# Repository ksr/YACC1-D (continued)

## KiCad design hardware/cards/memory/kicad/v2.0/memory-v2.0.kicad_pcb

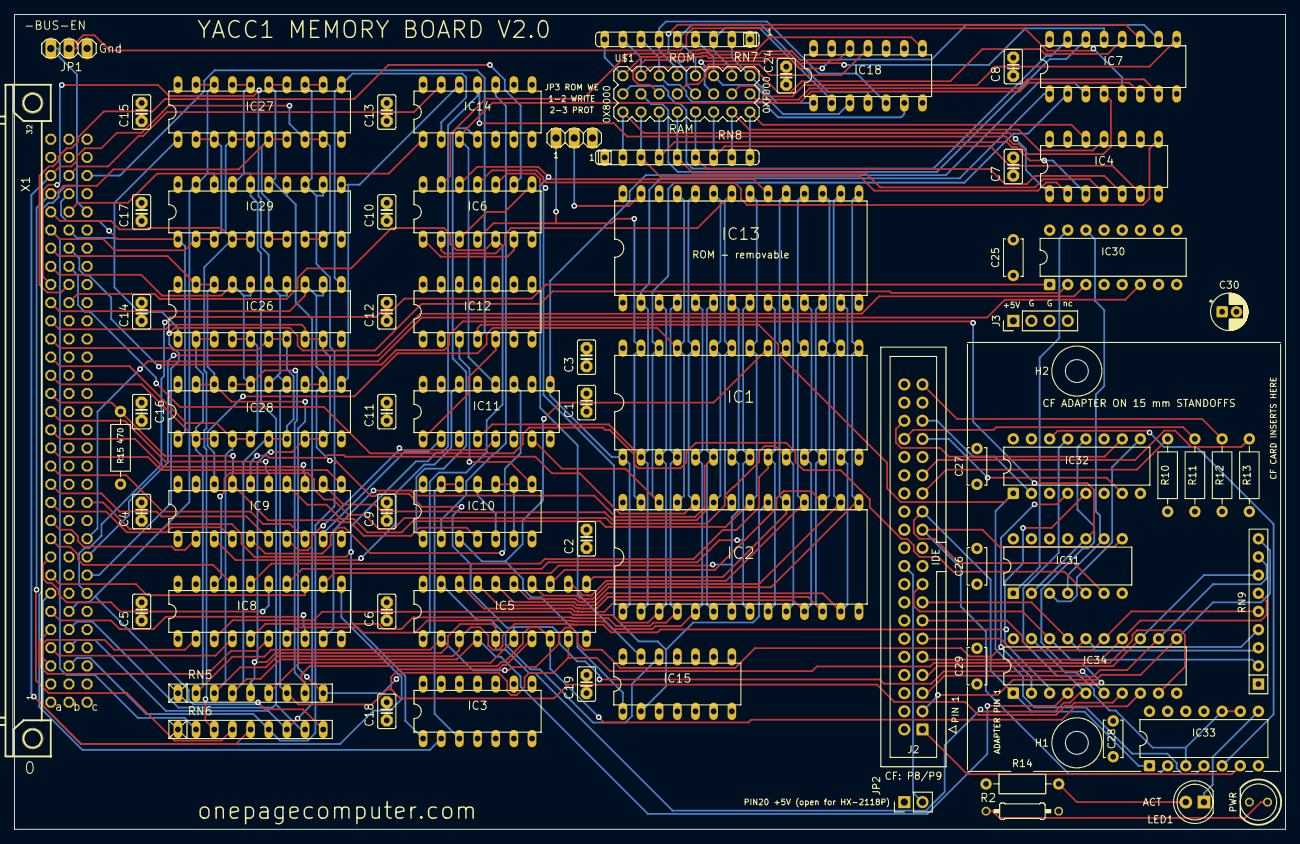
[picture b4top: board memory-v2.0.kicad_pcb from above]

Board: 4 copper layers, 177.8 x 114.0 mm, 74 parts (0 on the bottom side), 149 nets.

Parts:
C1, C2, C3, C4, C5, C6, C7, C8, C9, C10, C11, C12, C13, C14, C15, C16, C17, C18, C19, C24: C025-025X050
C25, C26, C27, C28, C29: 100n; C_Disc_D5.0mm_W2.5mm_P5.00mm
C30: 10u; CP_Radial_D5.0mm_P2.00mm
H1, H2: M3 standoff 15 mm (CF adapter); MountingHole_3.2mm_M3
IC1, IC2, IC13: DIL28-6
IC3: 74LS32N; DIL14
IC4, IC18: 74ALS30N; DIL14
IC5: 74LS245N; DIL20
IC6, IC14: 74LS04N; DIL14
IC7: 74LS138N; DIL16
IC8, IC9: 74LS244N; DIL20
IC10: 74ALS00N; DIL14
IC11: 74LS157N; DIL16
IC12: 74LS74N; DIL14
IC15: 74ALS11N; DIL14
IC26, IC27, IC28, IC29: 74LS374N; DIL20
IC30: 74LS138; DIP-16_W7.62mm
IC31: 74LS32; DIP-14_W7.62mm
IC32: 74LS175; DIP-16_W7.62mm
IC33: 74LS08; DIP-14_W7.62mm
IC34: 74LS245; DIP-20_W7.62mm
J2: IDE 40; IDC-Header_2x20_P2.54mm_Vertical
J3: POWER; PinHeader_1x04_P2.54mm_Vertical
JP1: 1X03
JP2: PIN20 5V; PinHeader_1x02_P2.54mm_Vertical
JP3: PINHD-1X3; 1X03
LED1: ACT yellow; LED_D5.0mm
PWR0: LED5MM
R2: 330; 0207_10
R10, R11, R12, R13: 10k; R_Axial_DIN0207_L6.3mm_D2.5mm_P10.16mm_Horizontal
R14: 1k; R_Axial_DIN0207_L6.3mm_D2.5mm_P10.16mm_Horizontal
R15: 470; R_Axial_DIN0207_L6.3mm_D2.5mm_P10.16mm_Horizontal
RN5, RN6: RN-9
RN7, RN8: SIL9
RN9: 10k x8; R_Array_SIP9
U$1: PIN_3X8
X1: FABC96R

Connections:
-BUS-EN: IC3.2, JP1.1, X1.C28
-HI-RAM: IC2.20, IC6.10, IC15.2
-IO-RD: IC31.5, X1.B25
-IO-WR: IC31.2, IC31.10, X1.B26
-LO-RAM: IC1.20, IC10.3, IC15.1
-MEM-RD: IC5.1, IC6.5, X1.B23
-MEM-WR: IC6.9, X1.B24
-RESET: IC12.4, IC32.1, IC33.4, X1.C30
-ROM-CS: IC6.12, IC13.20, IC15.13
-TMP-REG-LD0: IC14.1, X1.B28
-TMP-REG-LD1: IC14.13, X1.B30
-TMP-REG-RD0: IC26.1, IC27.1, X1.B27
-TMP-REG-RD1: IC28.1, IC29.1, X1.B29
-VMA: IC3.1, IC7.4, IC14.11, X1.C12
/Sheet 2/RAM0: IC4.1, RN8.2, U$1.17
/Sheet 2/RAM1: IC4.2, RN8.3, U$1.18
/Sheet 2/RAM2: IC4.3, RN8.4, U$1.19
/Sheet 2/RAM3: IC4.4, RN8.5, U$1.20
/Sheet 2/RAM4: IC4.5, RN8.6, U$1.21
/Sheet 2/RAM5: IC4.6, RN8.7, U$1.22
/Sheet 2/RAM6: IC4.11, RN8.8, U$1.23
/Sheet 2/RAM7: IC4.12, RN8.9, U$1.24
/Sheet 2/ROM0: IC18.12, RN7.9, U$1.1
/Sheet 2/ROM1: IC18.11, RN7.8, U$1.2
/Sheet 2/ROM2: IC18.6, RN7.7, U$1.3
/Sheet 2/ROM3: IC18.5, RN7.6, U$1.4
/Sheet 2/ROM4: IC18.4, RN7.5, U$1.5
/Sheet 2/ROM5: IC18.3, RN7.4, U$1.6
/Sheet 2/ROM6: IC18.2, RN7.3, U$1.7
/Sheet 2/ROM7: IC18.1, RN7.2, U$1.8
/Sheet 2/SEL0: IC7.15, U$1.9
/Sheet 2/SEL1: IC7.14, U$1.10
/Sheet 2/SEL2: IC7.13, U$1.11
/Sheet 2/SEL3: IC7.12, U$1.12
/Sheet 2/SEL4: IC7.11, U$1.13
/Sheet 2/SEL5: IC7.10, U$1.14
/Sheet 2/SEL6: IC7.9, U$1.15
/Sheet 2/SEL7: IC7.7, U$1.16
/Sheet 3/ROM-WE: IC13.27, JP3.2
/Sheet 7/-CFOE: IC33.3, IC33.9, IC33.10, IC34.19
/Sheet 7/-CFRESET: IC33.6, J2.1
/Sheet 7/-DASP: J2.39, R12.2
/Sheet 7/-DMACK: J2.29, R13.2
/Sheet 7/-IOR: IC31.6, IC33.1, IC34.1, J2.25
/Sheet 7/-IOW: IC31.8, IC33.2, J2.23
/Sheet 7/-P8SEL: IC30.15, IC31.1
/Sheet 7/-P9SEL: IC30.14, IC31.4, IC31.9
/Sheet 7/-PDIAG: J2.34, R11.2
/Sheet 7/-SRST: IC32.14, IC33.5
/Sheet 7/ACTK: IC33.8, LED1.1
/Sheet 7/CFD0: IC34.18, J2.17, RN9.2
/Sheet 7/CFD1: IC34.17, J2.15, RN9.3
/Sheet 7/CFD2: IC34.16, J2.13, RN9.4
/Sheet 7/CFD3: IC34.15, J2.11, RN9.5
/Sheet 7/CFD4: IC34.14, J2.9, RN9.6
/Sheet 7/CFD5: IC34.13, J2.7, RN9.7
/Sheet 7/CFD6: IC34.12, J2.5, RN9.8
/Sheet 7/CFD7: IC34.11, J2.3, RN9.9
/Sheet 7/DA0: IC32.2, J2.35
/Sheet 7/DA1: IC32.7, J2.33
/Sheet 7/DA2: IC32.10, J2.36
/Sheet 7/IORDY: J2.27, R10.2
/Sheet 7/LATCHCLK: IC31.3, IC32.9
/Sheet 7/LEDA2: LED1.2, R14.2
/Sheet 7/PIN20: J2.20, JP2.2
ADDR0: IC8.2, X1.A3
ADDR1: IC8.4, X1.A4
ADDR2: IC8.6, X1.A5
ADDR3: IC8.8, X1.A6
ADDR4: IC8.11, X1.A7
ADDR5: IC8.13, X1.A8
ADDR6: IC8.15, X1.A9
ADDR7: IC8.17, X1.A10
ADDR8: IC9.2, X1.A11
ADDR9: IC9.4, X1.A12
ADDR10: IC9.6, X1.A13
ADDR11: IC9.8, X1.A14
ADDR12: IC9.11, X1.A15
ADDR13: IC9.13, X1.A16
ADDR14: IC9.15, X1.A17
ADDR15: IC9.17, IC10.4, R15.1, X1.A18
BADDR0: IC1.10, IC2.10, IC8.18, IC13.10
BADDR1: IC1.9, IC2.9, IC8.16, IC13.9
BADDR2: IC1.8, IC2.8, IC8.14, IC13.8
BADDR3: IC1.7, IC2.7, IC8.12, IC13.7
BADDR4: IC1.6, IC2.6, IC8.9, IC13.6
BADDR5: IC1.5, IC2.5, IC8.7, IC13.5
BADDR6: IC1.4, IC2.4, IC8.5, IC13.4
BADDR7: IC1.3, IC2.3, IC8.3, IC13.3
BADDR8: IC1.25, IC2.25, IC9.18, IC13.25
BADDR9: IC1.24, IC2.24, IC9.16, IC13.24
BADDR10: IC1.21, IC2.21, IC9.14, IC13.21
BADDR11: IC1.23, IC2.23, IC9.12, IC13.23
BADDR12: IC1.2, IC2.2, IC7.1, IC11.4, IC13.2
BADDR13: IC1.26, IC2.26, IC7.2, IC11.7
BADDR14: IC1.1, IC2.1, IC7.3, IC11.9
BADDR15: IC7.6, IC11.12, IC14.3
BDATA0: IC1.11, IC2.11, IC5.18, IC13.11
BDATA1: IC1.12, IC2.12, IC5.17, IC13.12
BDATA2: IC1.13, IC2.13, IC5.16, IC13.13
BDATA3: IC1.15, IC2.15, IC5.15, IC13.15
BDATA4: IC1.16, IC2.16, IC5.14, IC13.16
BDATA5: IC1.17, IC2.17, IC5.13, IC13.17
BDATA6: IC1.18, IC2.18, IC5.12, IC13.18
BDATA7: IC1.19, IC2.19, IC5.11, IC13.19
DATA0: IC5.2, IC26.2, IC26.3, IC28.2, IC28.3, IC32.4, IC34.2, RN5.2, X1.A19
DATA1: IC5.3, IC26.4, IC26.5, IC28.4, IC28.5, IC32.5, IC34.3, RN5.3, X1.A20
DATA2: IC5.4, IC26.6, IC26.7, IC28.6, IC28.7, IC32.12, IC34.4, RN5.4, X1.A21
DATA3: IC5.5, IC26.8, IC26.9, IC28.8, IC28.9, IC32.13, IC34.5, RN5.5, X1.A22
DATA4: IC5.6, IC26.12, IC26.13, IC28.12, IC28.13, IC34.6, RN5.6, X1.A23
DATA5: IC5.7, IC26.14, IC26.15, IC28.14, IC28.15, IC34.7, RN5.7, X1.A24
DATA6: IC5.8, IC26.16, IC26.17, IC28.16, IC28.17, IC34.8, RN5.8, X1.A25
DATA7: IC5.9, IC26.18, IC26.19, IC28.18, IC28.19, IC34.9, RN5.9, X1.A26
DATA8: IC27.2, IC27.3, IC29.2, IC29.3, RN6.2, X1.A27
DATA9: IC27.4, IC27.5, IC29.4, IC29.5, RN6.3, X1.A28
DATA10: IC27.6, IC27.7, IC29.6, IC29.7, RN6.4, X1.A29
DATA11: IC27.8, IC27.9, IC29.8, IC29.9, RN6.5, X1.A30
DATA12: IC27.12, IC27.13, IC29.12, IC29.13, RN6.6, X1.B3
DATA13: IC27.14, IC27.15, IC29.14, IC29.15, RN6.7, X1.B4
DATA14: IC27.16, IC27.17, IC29.16, IC29.17, RN6.8, X1.B5
DATA15: IC27.18, IC27.19, IC29.18, IC29.19, RN6.9, X1.B6
FORCE-ROM: IC11.1, IC12.5
GND: C1.2, C2.2, C3.2, C4.2, C5.2, C6.2, C7.2, C8.2, C9.2, C10.2, C11.2, C12.2, C13.2, C14.2, C15.2, C16.2, C17.2, C18.2, C19.1, C24.1, C25.2, C26.2, C27.2, C28.2, C29.2, C30.2, IC1.14, IC2.14, IC3.4, IC3.5, IC3.7, IC3.9, IC3.10, IC3.12, IC3.13, IC4.7, IC5.10, IC6.7, IC7.8, IC8.1, IC8.10, IC8.19, IC9.1, IC9.10, IC9.19, IC10.7, IC11.8, IC11.15, IC12.2, IC12.7, IC12.10, IC12.11, IC12.12, IC12.13, IC13.14, IC14.7, IC15.3, IC15.4, IC15.5, IC15.7, IC15.9, IC15.10, IC15.11, IC18.7, IC26.10, IC27.10, IC28.10, IC29.10, IC30.4, IC30.5, IC30.8, IC31.7, IC31.12, IC31.13, IC32.8, IC33.7, IC33.12, IC33.13, IC34.10, J2.2, J2.19, J2.22, J2.24, J2.26, J2.28, J2.30, J2.37, J2.40, J3.2, J3.3, JP1.3, PWR0.K, R15.2, RN5.1, RN6.1, X1.A1, X1.A32, X1.B1, X1.B32, X1.C1, X1.C32
IO-ADDR0: IC30.1, X1.C7
IO-ADDR1: IC30.2, X1.C8
IO-ADDR2: IC30.3, X1.C9
IO-ADDR3: IC30.6, X1.C10
unnamed: IC1.22, IC2.22, IC6.2, IC13.22
unnamed: IC1.27, IC2.27, IC6.4, JP3.1
unnamed: IC4.8, IC6.11
unnamed: IC6.1, IC6.6
unnamed: IC6.3, IC6.8
unnamed: IC7.5, JP1.2
unnamed: IC10.1, IC14.4
unnamed: IC10.2, IC14.10
unnamed: IC10.5, IC10.11
unnamed: IC10.6, IC10.9, IC10.10
unnamed: IC10.8, IC12.3
unnamed: IC3.3, IC10.12, IC10.13
unnamed: IC9.9, IC11.2
unnamed: IC9.7, IC11.5
unnamed: IC9.5, IC11.11
unnamed: IC9.3, IC11.14
unnamed: IC14.2, IC26.11, IC27.11
unnamed: IC14.12, IC28.11, IC29.11
unnamed: IC5.19, IC15.12
unnamed: IC6.13, IC18.8
unnamed: PWR0.A, R2.1
VCC: C1.1, C2.1, C3.1, C4.1, C5.1, C6.1, C7.1, C8.1, C9.1, C10.1, C11.1, C12.1, C13.1, C14.1, C15.1, C16.1, C17.1, C18.1, C19.2, C24.2, C25.1, C26.1, C27.1, C28.1, C29.1, C30.1, IC1.28, IC2.28, IC3.14, IC4.14, IC5.20, IC6.14, IC7.16, IC8.20, IC9.20, IC10.14, IC11.3, IC11.6, IC11.10, IC11.13, IC11.16, IC12.1, IC12.14, IC13.28, IC14.14, IC15.14, IC18.14, IC26.20, IC27.20, IC28.20, IC29.20, IC30.16, IC31.14, IC32.16, IC33.14, IC34.20, J2.38, J3.1, JP2.1, JP3.3, R2.2, R10.1, R11.1, R12.1, R13.1, R14.1, RN7.1, RN8.1, RN9.1, X1.A2, X1.A31, X1.B2, X1.B31, X1.C2, X1.C31

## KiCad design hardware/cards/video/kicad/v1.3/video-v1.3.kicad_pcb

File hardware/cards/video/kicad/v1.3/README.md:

# video-v1.3 — KiCad design for the video card

**Superseded by `../v2.0/` (2026-10-22), which builds on it; kept as the DOTS-jumper design. Not ordered.**

(Was the master from 2026-10-22.) v1.3 is `../v1.2/` (the bench state of 2026-10-21) with one
jumper that chooses **6 or 8 dots a character**, and a new board: **4 layers, routed from scratch** - In1.Cu a solid GND
plane, In2.Cu a solid VCC plane, every signal routed anew, GND and VCC never routed (every power pin is a through-hole
pad on its plane). The outline, the bus connector X1 and the placement are v1.2's; the parts v1.3 adds sit beside IC28.
`tools/eagle_to_kicad_all.py` never writes here (`MASTER` marker file). `./build.sh` rebuilds the board and every report
and checks them (needs KiCad 10 and Freerouting 1.9).

## The two modes

One 12 MHz crystal (Q2, SV4 on 1-2) serves both:

| DOTS jumper (JP2) | IC28 divides by | character clock | screen | 6845 R0..R9 | dots across | EPROM time a character |
|---|---|---|---|---|---|---|
| open (R15 pulls DOTS high) | 6 | 2.0 MHz | **80 x 24** | 126, 80, 98, 10, 31, 6, 24, 27, 0, 7 | 480 | 500 ns |
| fitted (DOTS to GND) | 8 | 1.5 MHz | **64 x 24** | 94, 64, 75, 8, 31, 6, 24, 27, 0, 7 | 512 | 667 ns |

Both 15.75 kHz / 60 Hz. The 64 x 24 table is the one proven on a TV-rate monitor on 2026-10-21 (9 MHz / 6 = the same
1.5 MHz); the 80 x 24 table is centred in that monitor's measured visible window (about 10.3-58.3 us after the sync
starts: the text runs 14.5-54.5 us). `python3 tools/vidsim.py testcard --card v1.3 --dots 6|8 --png card.png` draws
each mode; `vidsim.py chargen --card v1.3` writes the EPROM (`firmware/video/chargen-v13.bin`).

## Changes since v1.2 (schematic)

| # | Change | Pins |
|---|---|---|
| 1 | **IC28 (74163) divides by 16 - P, loading P on its carry** | -CLR (1) to VCC; data A (3) GND, B (4) **DOTS**, C (5) GND, D (6) VCC: P = 8 (/8) or 10 (/6); -LOAD (9) = CHARCLOCK; RCO (15) = net `RCO`; QA (14) unconnected; ENT/ENP (10, 7) stay on N$73 (R10). CRTCCLOCK stays QC (12) -> IC17 21 |
| 2 | **CHARCLOCK = NOT RCO** | IC19/C both inputs (9, 10) on `RCO` (were QA and CRTCCLOCK): one dot low at count 15 in both modes, the same pulse the 74LS166 load and IC22/IC23 get in v1.2 |
| 3 | **DOTS jumper JP2** (2-pin header, silk "DOTS: ON=8") + **R15 4.7k** pull-up | JP2 1 = DOTS, 2 = GND; R15 VCC - DOTS. Fitted = 8 dots, open = 6 dots |
| 4 | **Font select: DOTS on EPROM A10** | IC25 pin 19 (was GND): the 8-dot font at $000, the 6-dot font at $400; A9, A11 stay GND |
| 5 | **DOTS readable at `$D801` bit 0** | latch IC2 1D (pin 3) on DOTS (was JP1 pin 1, now unconnected): 1 = 6 dots, 0 = 8. IC2 LE (pin 11) to VCC (was JP1 pin 13, which floated): the latch is transparent by design; JP1 pin 13 unconnected |
| 5a | **Card ID at `$D801` bit 2** (2026-10-22) | latch IC2 3D (pin 7) to GND (was JP1 pin 4, now unconnected, no-connect flag): bit 2 = 0 says "V1.3" to `ROM 2026-10-22` and later, which then reads DOTS on bit 0 for 80 x 24 or 64 x 24; the V1.0-V1.2 card reads bit 2 = 1 (a jumper on its JP1 3-4) and keeps its 11.0592 MHz table |
| 6 | **IC24 (74LS166) loads all eight bits** | A, B, C (2, 3, 4; were GND) to EPROM O0, O1, O2 (IC25 9, 10, 11) on nets `CG0..CG2`. In 6-dot mode the next load comes after 6 shifts, so only O7..O2 are seen |
| 7 | values, title | Q2 **12MHz**; IC25 **2732 (chargen-v13)**; silkscreen "YACC1 Video Card V1.3" |

Unchanged from v1.2: RS on ADDR1, LPSTB to GND, the R13 / R14 4.7k pull-ups, E without the one-shot (IC1 pin 2 on VCC).
Characters stay 8 scan lines tall in both modes (R9 = 7): taller ones need RA3 to the EPROM and would break the
proposed graphics overlay's 8-plane addressing (`BACKLOG.md`).

**The 6845's clock in 6-dot mode.** QC over counts 10..15 is low for 2 dots and high for 4: **167 ns low / 333 ns high**
at 12 MHz (8-dot mode: 333 / 333 ns). Motorola's MC6845 data sheet gives a minimum clock pulse width of 160 ns low and
200 ns high (**To verify:** from the data sheet as remembered - the tree's `docs/BYTE 6845.pdf` is a scan without the
timing table). 167 ns against 160 ns is a margin of only 7 ns. Fit a faster grade (MC68A45 / MC68B45, or an HD6845S) for
the 6-dot mode, or check the fitted part's sheet; 8-dot mode has ample margin. The ROM's support (read `$D801` bit 0 at
reset, pick 80 or 64 columns and the table) is the next step (`BACKLOG.md`, "Video v1.3").

**The EPROM in 6-dot mode** gets 500 ns a character; the MBM2732A is a 450 ns part: it works with little slack. A faster
part (a 2732A-25, or a 27C32/2764 at 250 ns with a socket adapter) removes the worry.

## The board

| | |
|---|---|
| Layers | 4, 1.6 mm (JLCPCB-style 4-layer): F.Cu signals, **In1.Cu GND plane**, **In2.Cu VCC plane**, B.Cu signals |
| Rules (`video-v1.3.kicad_dru`, the project's net classes) | as the memory card v2.0: signal tracks 0.25 mm, clearance 0.2 mm, vias 0.8 / 0.4 mm, copper to edge 0.5 mm; plane antipads 0.3 mm, thermal reliefs 0.4 mm gap / 0.5 mm spokes; class Power = GND, VCC: not routed |
| Outline, X1, placement | v1.2's (177.8 x 114.0 mm); **JP2** at (179.7, 116.6), pads horizontal, right of IC28; **R15** vertical at x = 185.4 (pads at y 113.0 / 120.62); the "DOTS: ON=8" label below JP2 |
| Route | Freerouting 1.9 on a 2-signal-layer copy (planes dropped, `-inc Power`), one run per DSN component order (seeds 0-7, in parallel), the best kept: **seed 7: 0 unrouted, 39 vias, 8.41 m of 0.25 mm track** (F.Cu 4.29 m, B.Cu 4.13 m; rebuilt 2026-10-22 with the card ID). The other seeds: 39-52 vias, seed 1 with 3 clearance findings |
| Planes | each one solid piece (GND 17,737 mm², VCC 17,724 mm² of the 20,270 mm² board; the rest antipads), plus a few 0.8 mm² slivers between X1's pins |

## Proof

- Schematic vs board (`tools/kicad/compare_netlists.py`): **MATCH, 115/115 nets** (116 before the card ID: N$13 is gone).
- DRC: **0 unconnected** (every GND/VCC pad reaches its net through its plane only: the planes connect), no clearance,
  short or dangling-track finding; the residue is v1.2's cosmetic set, unchanged by type and count: silk_over_copper
  199, silk_overlap 15, silk_edge_clearance 8, lib_footprint_mismatch 3, items_not_allowed 2 (X1's mounting holes in
  X1's own keepout), text_height 2. Schematic parity: footprint_symbol_mismatch 16 and net_conflict 29, the conversion's
  inherited value texts and its "unconnected-(...)" pins, as v1.2; the three net_conflict items v1.2 lacks are the pins
  v1.3 leaves unconnected (IC28 14, JP1 1, JP1 4, JP1 13), and v1.2's for IC28 15 and IC25 9-11 are gone (now used).
- ERC: endpoint_off_grid 35, isolated_pin_label 56, pin_to_pin 9 - v1.2's cosmetic set, unchanged.
- `gen_v13.py verify`: every change above checked pin by pin in the schematic netlist **and** on the board's pads; no
  track on GND or VCC; copper layers F.Cu, In1.Cu, In2.Cu, B.Cu; one plane each.

## Files

| File | What it is |
|---|---|
| `video-v1.3.kicad_pro`, `video-v1.3.kicad_dru` | project and rules (written by `gen_v13.py project`) |
| `video-v1.3.kicad_sch` + `-sheet1/2` | schematic (two sheets, as the Eagle original) |
| `video-v1.3.kicad_pcb` | the 4-layer board (written by `build.sh`) |
| `video-v1.3-eagle.kicad_sym`, `video-v1.3-eagle.pretty/` | project libraries; v1.3 adds the symbol `con-lstb_MA02-1` and KiCad's `PinHeader_1x02_P2.54mm_Vertical` footprint |
| `gen_v13.py`, `build.sh` | the board generator (project, board, dsn, shuffle, ses, stats, silk, verify) and the build |
| `reports/` | netlist + `netlist-compare.txt` (proof), `erc.json`, `drc.json`, schematic PDF, top/bottom renders |

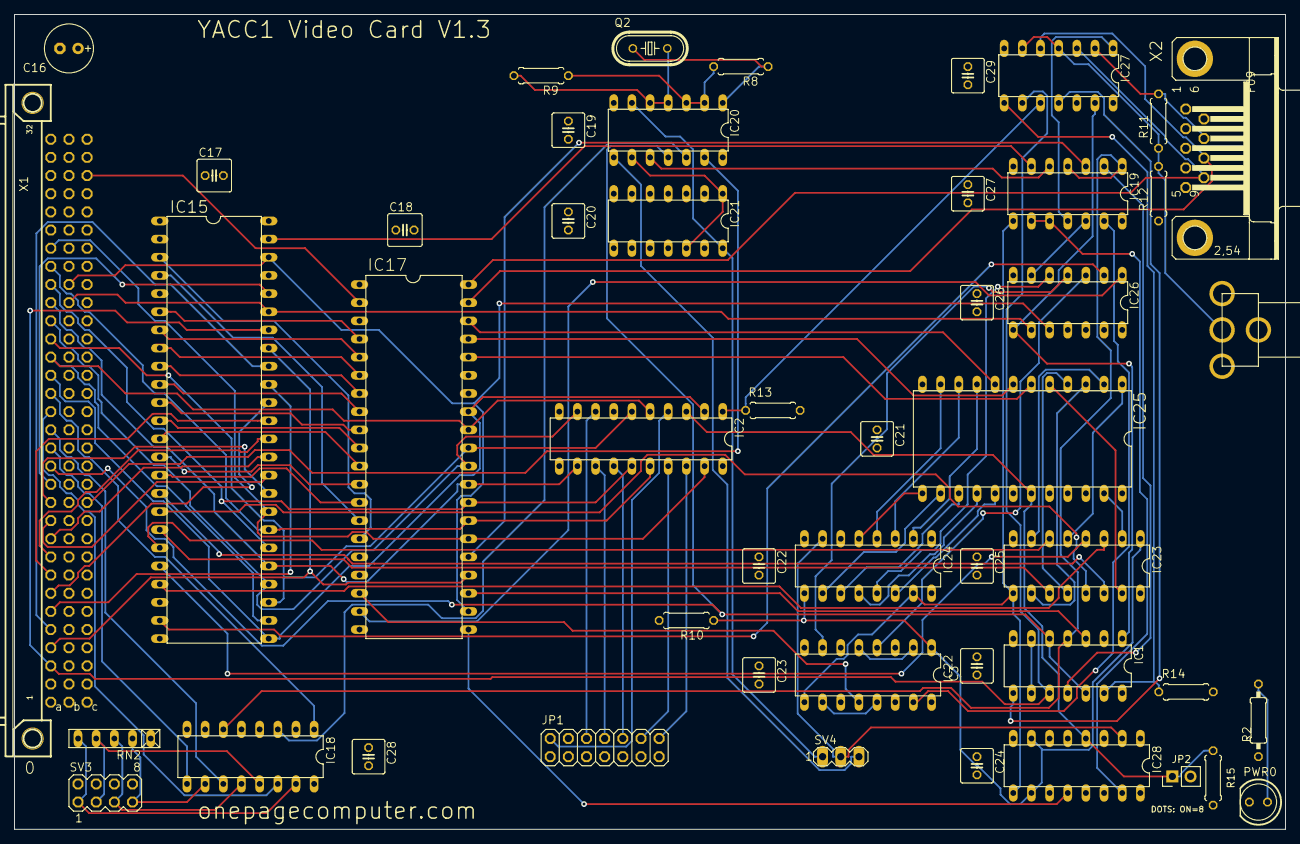
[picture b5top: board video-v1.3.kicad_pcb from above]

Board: 4 copper layers, 177.8 x 114.0 mm, 49 parts (0 on the bottom side), 115 nets.

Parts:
C3, C17, C18, C19, C20, C21, C22, C23, C24, C25, C26, C27, C28, C29: .1; C025-050X050
C16: 10.0; E2,5-7
IC1: 74ALS08N; DIL14
IC2: 74LS373N; DIL20
IC15: VRAM; DIL48
IC17: 6845; DIL40
IC18: 74S85N; DIL16
IC19: 74LS00N; DIL14
IC20: 74LS04N; DIL14
IC21: 74LS90N; DIL14
IC22: 74LS175N; DIL16
IC23: 74LS174N; DIL16
IC24: 74LS166N; DIL16
IC25: 2732 (chargen-v13); DIL24
IC26: 74LS86N; DIL14
IC27: 7416N; DIL14
IC28: 74163; DIL16
JP1: PINHD-2X7; 2X07
JP2: DOTS 8=ON; PinHeader_1x02_P2.54mm_Vertical
PWR0: LED5MM
Q2: 12MHz; HC49U-V
R2: 330; 0207_10
R8, R9, R10: 1K; 0207_7
R11: 33; 0207_7
R12: 270; 0207_7
R13, R14, R15: 4.7K; 0207_7
RN2: RN-5
SV3: MA04-2
SV4: MA03-1
U$3: RCA
X1: FABC96R
X2: F09HP

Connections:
-MEM-RD: IC15.43, IC26.9, X1.B23
-MEM-WR: IC15.46, IC17.22, IC26.10, X1.B24
-RESET: IC17.2, X1.C30
-VMA: IC20.13, X1.C12
ADDR0: IC1.10, IC15.42, IC27.9, X1.A3
ADDR1: IC15.41, IC17.24, X1.A4
ADDR2: IC15.40, X1.A5
ADDR3: IC15.39, X1.A6
ADDR4: IC15.38, X1.A7
ADDR5: IC15.37, X1.A8
ADDR6: IC15.36, X1.A9
ADDR7: IC15.35, X1.A10
ADDR8: IC15.34, X1.A11
ADDR9: IC15.33, X1.A12
ADDR10: IC15.44, X1.A13
ADDR11: IC1.5, IC1.12, IC20.11, X1.A14
ADDR12: IC18.9, X1.A15
ADDR13: IC18.11, X1.A16
ADDR14: IC18.14, X1.A17
ADDR15: IC18.1, X1.A18
BOARDSEL: IC1.4, IC18.6, IC19.1, IC19.4
CG0: IC24.2, IC25.9
CG1: IC24.3, IC25.10
CG2: IC24.4, IC25.11
CHARCLOCK: IC19.8, IC22.9, IC23.9, IC24.15, IC28.9
CLK: IC1.3, IC17.23
CRTCCLOCK: IC17.21, IC28.12
DATA0: IC2.2, IC15.25, IC17.33, X1.A19
DATA1: IC2.5, IC15.26, IC17.32, X1.A20
DATA2: IC2.6, IC15.27, IC17.31, X1.A21
DATA3: IC2.9, IC15.28, IC17.30, X1.A22
DATA4: IC2.12, IC15.29, IC17.29, X1.A23
DATA5: IC2.15, IC15.30, IC17.28, X1.A24
DATA6: IC2.16, IC15.31, IC17.27, X1.A25
DATA7: IC2.19, IC15.32, IC17.26, X1.A26
DOTCLOCK: IC24.7, IC28.2, SV4.2
DOTS: IC2.3, IC25.19, IC28.4, JP2.1, R15.2
GND: C3.2, C16.-, C17.2, C18.2, C19.2, C20.2, C21.2, C22.2, C23.2, C24.2, C25.2, C26.2, C27.2, C28.2, C29.2, IC1.7, IC2.7, IC2.10, IC15.1, IC15.5, IC15.24, IC15.45, IC17.1, IC17.3, IC18.2, IC18.4, IC18.8, IC19.7, IC20.7, IC21.2, IC21.3, IC21.6, IC21.7, IC21.10, IC22.8, IC23.8, IC24.1, IC24.6, IC24.8, IC25.12, IC25.18, IC25.20, IC25.21, IC25.22, IC26.7, IC26.12, IC26.13, IC27.7, IC28.3, IC28.5, IC28.8, JP1.5, JP2.2, PWR0.K, SV3.2, SV3.4, SV3.6, SV3.8, U$3.S1, U$3.S2, U$3.S3, X1.A1, X1.A32, X1.B1, X1.B32, X1.C1, X1.C32, X2.1
unnamed: IC1.1, IC26.8, IC27.13
unnamed: IC1.11, IC19.2
unnamed: IC1.13, IC27.8, R14.1
unnamed: IC1.8, IC27.11
unnamed: IC2.18, JP1.14
unnamed: IC2.17, JP1.12
unnamed: IC2.14, JP1.10
unnamed: IC2.13, JP1.8
unnamed: PWR0.A, R2.1
unnamed: IC2.8, JP1.6
unnamed: IC2.4, JP1.2
unnamed: IC2.1, IC27.10, R13.1
unnamed: IC1.6, IC1.9
unnamed: IC18.10, RN2.2, SV3.7
unnamed: IC18.12, RN2.3, SV3.5
unnamed: IC18.13, RN2.4, SV3.3
unnamed: IC18.15, RN2.5, SV3.1
unnamed: IC15.47, IC19.6
unnamed: IC20.1, Q2.1, R8.1
unnamed: IC20.4, IC20.5, Q2.2, R9.2
unnamed: IC20.2, IC20.3, R8.2, R9.1
unnamed: IC20.6, IC21.14, SV4.1
unnamed: IC20.9, IC21.1, IC21.12
unnamed: IC20.8, SV4.3
unnamed: IC22.2, IC22.5
unnamed: IC24.5, IC25.13
unnamed: IC24.10, IC25.14
unnamed: IC24.11, IC25.15
unnamed: IC24.12, IC25.16
unnamed: IC24.14, IC25.17
unnamed: IC23.2, IC25.23
unnamed: IC23.5, IC25.1
unnamed: IC23.7, IC25.2
unnamed: IC23.10, IC25.3
unnamed: IC23.12, IC25.4
unnamed: IC23.15, IC25.5
unnamed: IC22.1, IC23.1, IC24.9, IC28.7, IC28.10, R10.1
unnamed: IC17.19, IC26.1
unnamed: IC22.4, IC26.3
unnamed: IC22.7, IC26.4
unnamed: IC24.13, IC26.5
unnamed: IC22.10, IC22.13
unnamed: IC17.18, IC22.12
unnamed: IC19.12, IC26.6
unnamed: IC19.13, IC22.15
unnamed: IC17.40, IC27.3, X2.9
unnamed: IC17.39, IC27.5, X2.8
unnamed: IC19.11, IC27.1
unnamed: IC27.4, IC27.6, R11.1, R12.2, U$3.C1
unnamed: IC27.2, R11.2, X2.7
unnamed: IC19.5, IC20.10
unnamed: IC18.3, IC20.12
unnamed: IC17.25, IC19.3
RCO: IC19.9, IC19.10, IC28.15
VADDR0: IC15.6, IC17.4
VADDR1: IC15.7, IC17.5
VADDR2: IC15.8, IC17.6
VADDR3: IC15.9, IC17.7
VADDR4: IC15.10, IC17.8
VADDR5: IC15.11, IC17.9
VADDR6: IC15.12, IC17.10
VADDR7: IC15.13, IC17.11
VADDR8: IC15.14, IC17.12
VADDR9: IC15.15, IC17.13
VADDR10: IC15.4, IC17.14
VADDR11: IC15.3, IC17.15
VCC: C3.1, C16.+, C17.1, C18.1, C19.1, C20.1, C21.1, C22.1, C23.1, C24.1, C25.1, C26.1, C27.1, C28.1, C29.1, IC1.2, IC1.14, IC2.11, IC2.20, IC15.2, IC15.48, IC17.20, IC18.16, IC19.14, IC20.14, IC21.5, IC22.16, IC23.16, IC24.16, IC25.24, IC26.14, IC27.14, IC28.1, IC28.6, IC28.16, JP1.3, R2.2, R10.2, R12.1, R13.2, R14.2, R15.1, RN2.1, X1.A2, X1.A31, X1.B2, X1.B31, X1.C2, X1.C31
VDATA0: IC15.16, IC23.14
VDATA1: IC15.17, IC23.13
VDATA2: IC15.18, IC23.11
VDATA3: IC15.19, IC23.6
VDATA4: IC15.20, IC23.4
VDATA5: IC15.21, IC23.3
VDATA7: IC15.23, IC26.2
VROWS0: IC17.38, IC25.8
VROWS1: IC17.37, IC25.7
VROWS2: IC17.36, IC25.6

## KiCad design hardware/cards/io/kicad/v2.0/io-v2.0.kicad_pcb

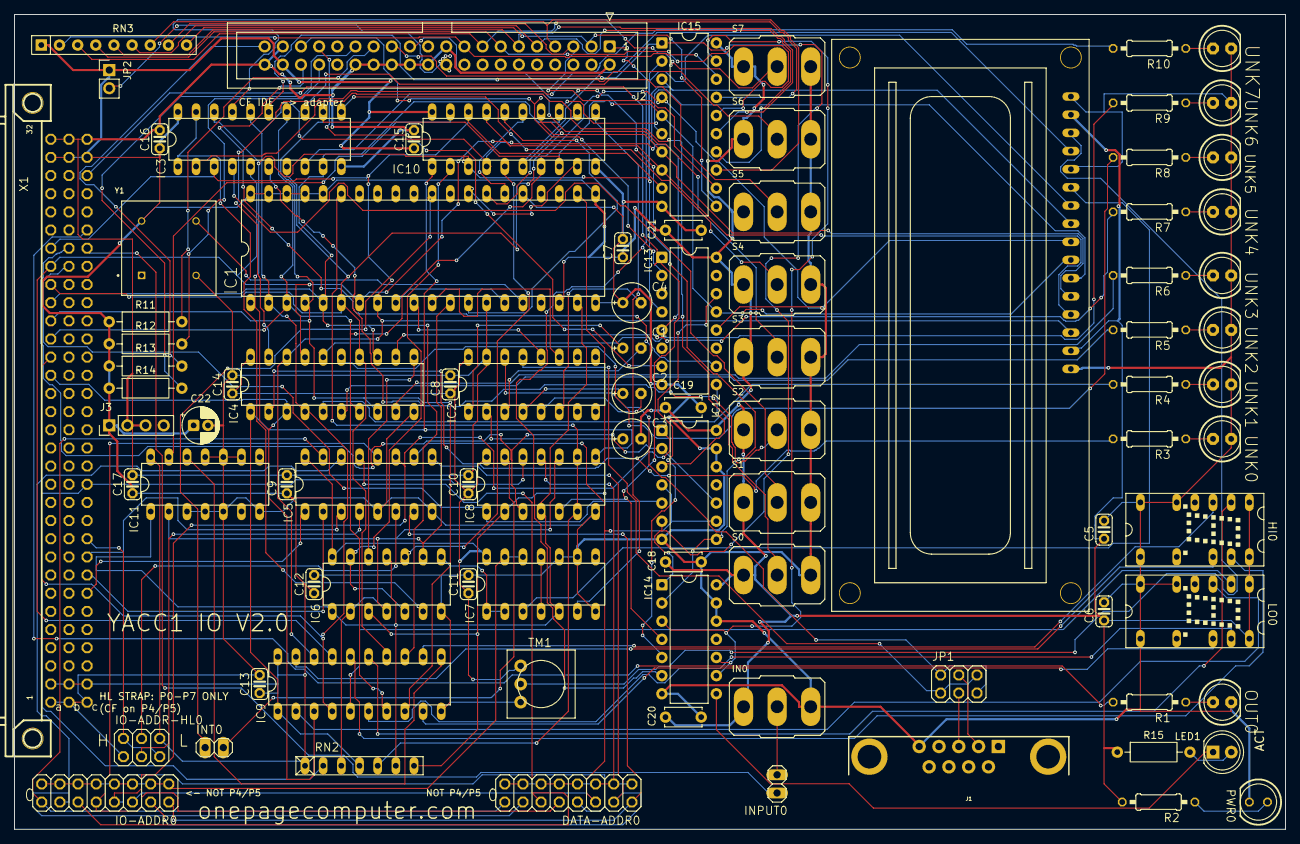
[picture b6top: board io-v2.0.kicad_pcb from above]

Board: 2 copper layers, 177.8 x 114.0 mm, 90 parts (0 on the bottom side), 128 nets.

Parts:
C1, C2, C3, C4: E2,5-6E
C5, C6, C7, C8, C9, C10, C11, C12, C13, C14, C15, C16, C17: C025-024X044
C18, C19, C20, C21: 100n; C_Disc_D5.0mm_W2.5mm_P5.00mm
C22: 10u; CP_Radial_D5.0mm_P2.00mm
DATA-ADDR0: 2X08
HI0: HTIL311A
IC1: DIL40
IC2: MAX232; DIL16
IC3: 74LS244N; DIL20
IC4, IC9, IC10: 74273N; DIL20
IC5: 74LS138N; DIL16
IC6, IC11: 74LS10N; DIL14
IC7: 74LS00N; DIL14
IC8: 74LS06N; DIL14
IC12: 74LS32; DIP-14_W7.62mm
IC13: 74LS175; DIP-16_W7.62mm
IC14: 74LS08; DIP-14_W7.62mm
IC15: 74LS245; DIP-20_W7.62mm
IN0: M9040P
INPUT0: 1X02
INT0: 1X02
IO-ADDR0: 2X08
IO-ADDR-HL0: 2X03
J1: DB9
J2: IDE 40; IDC-Header_2x20_P2.54mm_Vertical
J3: POWER; PinHeader_1x04_P2.54mm_Vertical
JP1: PINHD-2X3; 2X03
JP2: PIN20 5V; PinHeader_1x02_P2.54mm_Vertical
LED1: ACT yellow; LED_D5.0mm
LO0: HTIL311A
OUT0: LED5MM
PWR0: LED5MM
R1, R3, R4, R5, R6, R7, R8, R9, R10: 0207_10
R2: 330; 0207_10
R11, R12, R13, R14: 10k; R_Axial_DIN0207_L6.3mm_D2.5mm_P10.16mm_Horizontal
R15: 1k; R_Axial_DIN0207_L6.3mm_D2.5mm_P10.16mm_Horizontal
RN2: RN-7
RN3: 10k x8; R_Array_SIP9
S0, S1, S2, S3, S4, S5, S6, S7: M9040P
TM1: 10k; TRIM-3386
UNK0, UNK1, UNK2, UNK3, UNK4, UNK5, UNK6, UNK7: LED5MM
X1: FABC96R
X2: HD44780LCD-1602; LCD1602
Y1: ECS-2100AX-200

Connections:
-B-RESET: IC4.1, IC8.8, IC9.1, IC10.1, RN2.4
-INT: IC8.12, RN2.2, X1.C13
-IO-RD: IC8.1, IC12.5, X1.B25
-IO-SEL4: DATA-ADDR0.8, IC5.11, IC12.1, IO-ADDR0.8
-IO-SEL5: DATA-ADDR0.6, IC5.10, IC12.4, IC12.9, IO-ADDR0.6
-IO-WR: IC8.3, IC12.2, IC12.10, X1.B26
-RESET: IC8.5, IC13.1, IC14.4, X1.C30
/Sheet 2/ICLK: IC1.9, IC1.15
/Sheet 2/RX: IC1.10, IC2.12
/Sheet 2/RX-IN: IC2.13, JP1.1, JP1.6
/Sheet 2/TX-OUT: IC2.14, JP1.2, JP1.5
/Sheet 5/-IO-ADDRSEL: IC7.12, IC7.13, IO-ADDR0.1, IO-ADDR0.3, IO-ADDR0.5, IO-ADDR0.7, IO-ADDR0.9, IO-ADDR0.11, IO-ADDR0.13, IO-ADDR0.15
/Sheet 5/-IO-DATASEL: DATA-ADDR0.1, DATA-ADDR0.3, DATA-ADDR0.5, DATA-ADDR0.7, DATA-ADDR0.9, DATA-ADDR0.11, DATA-ADDR0.13, DATA-ADDR0.15, IC8.11
/Sheet 5/-IO-SEL0: DATA-ADDR0.16, IC5.15, IO-ADDR0.16
/Sheet 5/-IO-SEL1: DATA-ADDR0.14, IC5.14, IO-ADDR0.14
/Sheet 5/-IO-SEL2: DATA-ADDR0.12, IC5.13, IO-ADDR0.12
/Sheet 5/-IO-SEL3: DATA-ADDR0.10, IC5.12, IO-ADDR0.10
/Sheet 5/-IO-SEL6: DATA-ADDR0.4, IC5.9, IO-ADDR0.4
/Sheet 5/-IO-SEL7: DATA-ADDR0.2, IC5.7, IO-ADDR0.2
/Sheet 7/-CFOE: IC14.3, IC14.9, IC14.10, IC15.19
/Sheet 7/-CFRESET: IC14.6, J2.1
/Sheet 7/-DASP: J2.39, R13.2
/Sheet 7/-DMACK: J2.29, R14.2
/Sheet 7/-IOR: IC12.6, IC14.1, IC15.1, J2.25
/Sheet 7/-IOW: IC12.8, IC14.2, J2.23
/Sheet 7/-PDIAG: J2.34, R12.2
/Sheet 7/-SRST: IC13.14, IC14.5
/Sheet 7/ACTK: IC14.8, LED1.1
/Sheet 7/CFD0: IC15.18, J2.17, RN3.2
/Sheet 7/CFD1: IC15.17, J2.15, RN3.3
/Sheet 7/CFD2: IC15.16, J2.13, RN3.4
/Sheet 7/CFD3: IC15.15, J2.11, RN3.5
/Sheet 7/CFD4: IC15.14, J2.9, RN3.6
/Sheet 7/CFD5: IC15.13, J2.7, RN3.7
/Sheet 7/CFD6: IC15.12, J2.5, RN3.8
/Sheet 7/CFD7: IC15.11, J2.3, RN3.9
/Sheet 7/DA0: IC13.2, J2.35
/Sheet 7/DA1: IC13.7, J2.33
/Sheet 7/DA2: IC13.10, J2.36
/Sheet 7/IORDY: J2.27, R11.2
/Sheet 7/LATCHCLK: IC12.3, IC13.9
/Sheet 7/LEDA2: LED1.2, R15.2
/Sheet 7/PIN20: J2.20, JP2.2
DATA0: IC1.1, IC3.18, IC4.3, IC9.3, IC10.3, IC13.4, IC15.2, X1.A19, X2.7
DATA1: IC1.2, IC3.16, IC4.4, IC9.4, IC10.4, IC13.5, IC15.3, X1.A20, X2.8
DATA2: IC1.3, IC3.14, IC4.7, IC9.7, IC10.7, IC13.12, IC15.4, X1.A21, X2.9
DATA3: IC1.4, IC3.12, IC4.8, IC9.8, IC10.8, IC13.13, IC15.5, X1.A22, X2.10
DATA4: IC1.5, IC3.9, IC4.13, IC9.13, IC10.13, IC15.6, X1.A23, X2.11
DATA5: IC1.6, IC3.7, IC4.14, IC9.14, IC10.14, IC15.7, X1.A24, X2.12
DATA6: IC1.7, IC3.5, IC4.17, IC9.17, IC10.17, IC15.8, X1.A25, X2.13
DATA7: IC1.8, IC3.3, IC4.18, IC9.18, IC10.18, IC15.9, X1.A26, X2.14
GND: C4.+, C5.2, C6.2, C7.2, C8.2, C9.2, C10.2, C11.2, C12.2, C13.2, C14.2, C15.2, C16.2, C17.2, C18.2, C19.2, C20.2, C21.2, C22.2, HI0.5, HI0.7, HI0.8, IC1.14, IC1.20, IC1.25, IC2.15, IC3.10, IC4.10, IC5.5, IC5.8, IC6.7, IC7.7, IC7.9, IC7.10, IC8.7, IC9.10, IC10.10, IC11.3, IC11.4, IC11.5, IC11.7, IC11.9, IC11.10, IC11.11, IC12.7, IC12.12, IC12.13, IC13.8, IC14.7, IC14.12, IC14.13, IC15.10, IN0.3, IO-ADDR-HL0.1, J1.5, J2.2, J2.19, J2.22, J2.24, J2.26, J2.28, J2.30, J2.37, J2.40, J3.2, J3.3, LO0.5, LO0.7, LO0.8, OUT0.K, PWR0.K, S0.3, S1.3, S2.3, S3.3, S4.3, S5.3, S6.3, S7.3, TM1.3, UNK0.K, UNK1.K, UNK2.K, UNK3.K, UNK4.K, UNK5.K, UNK6.K, UNK7.K, X1.A1, X1.A32, X1.B1, X1.B32, X1.C1, X1.C32, X2.1, X2.5, X2.16, Y1.4
IN: INPUT0.1, X1.C26
IO-ADDR0: IC5.1, X1.C7
IO-ADDR1: IC5.2, X1.C8
IO-ADDR2: IC5.3, X1.C9
IO-ADDR3: IO-ADDR-HL0.2, IO-ADDR-HL0.5, X1.C10
IO-RD: IC1.22, IC6.3, IC8.2, RN2.7
IO-SELDATA: IC1.12, IC6.2, IC6.4, IC6.9, IC8.10, IC11.2, RN2.3
IO-WR: IC1.19, IC6.1, IC6.11, IC7.5, IC8.4, IC11.1, RN2.6
LCD-ENABLE: IC6.10, IC10.5
LCD-REGISTER: IC10.6, X2.4
unnamed: HI0.3, IC9.12
unnamed: HI0.2, IC9.15
unnamed: HI0.13, IC9.16
unnamed: HI0.12, IC9.19
unnamed: IC1.30, INT0.1
unnamed: IC1.11, IC2.11
unnamed: IC1.16, Y1.5
unnamed: C1.+, IC2.1
unnamed: C1.-, IC2.3
unnamed: C2.+, IC2.4
unnamed: C2.-, IC2.5
unnamed: C3.+, IC2.2
unnamed: C4.-, IC2.6
unnamed: IC3.2, S0.2
unnamed: IC3.4, S1.2
unnamed: IC3.6, S2.2
unnamed: IC3.8, S3.2
unnamed: IC3.1, IC3.19, IC6.6
unnamed: IC3.11, S4.2
unnamed: IC3.13, S5.2
unnamed: IC3.15, S6.2
unnamed: IC3.17, S7.2
unnamed: IC4.11, IC6.12
unnamed: IC4.2, R3.2
unnamed: IC4.5, R4.2
unnamed: IC4.6, R5.2
unnamed: IC4.9, R6.2
unnamed: IC4.12, R7.2
unnamed: IC4.15, R8.2
unnamed: IC4.16, R9.2
unnamed: IC4.19, R10.2
unnamed: IC5.6, IO-ADDR-HL0.4
unnamed: IC5.4, IO-ADDR-HL0.3
unnamed: IC6.8, IC7.1, IC7.2
unnamed: IC7.3, X2.6
unnamed: IC7.4, IC7.11
unnamed: IC8.13, INT0.2
unnamed: IC9.2, LO0.3
unnamed: IC9.5, LO0.2
unnamed: IC9.6, LO0.13
unnamed: IC9.9, LO0.12
unnamed: IC7.6, IC10.11
unnamed: IC9.11, IC11.12
unnamed: IN0.2, INPUT0.2
unnamed: J1.2, JP1.4
unnamed: J1.3, JP1.3
unnamed: OUT0.A, R1.1
unnamed: PWR0.A, R2.1
unnamed: R3.1, UNK0.A
unnamed: R4.1, UNK1.A
unnamed: R5.1, UNK2.A
unnamed: R6.1, UNK3.A
unnamed: R7.1, UNK4.A
unnamed: R8.1, UNK5.A
unnamed: R9.1, UNK6.A
unnamed: R10.1, UNK7.A
unnamed: TM1.2, X2.3
OUT: R1.2, X1.C27
RESET: IC1.35, IC8.6, IC8.9, RN2.5
SWITCH-LED: IC6.5, IC6.13, IC10.2
TIL311: IC10.19, IC11.13
UART-A0: IC1.28, IC10.9
UART-A1: IC1.27, IC10.12
UART-A2: IC1.26, IC10.15
UART-CS: IC1.13, IC10.16
VCC: C3.-, C5.1, C6.1, C7.1, C8.1, C9.1, C10.1, C11.1, C12.1, C13.1, C14.1, C15.1, C16.1, C17.1, C18.1, C19.1, C20.1, C21.1, C22.1, HI0.1, HI0.14, IC1.18, IC1.21, IC1.36, IC1.37, IC1.38, IC1.39, IC1.40, IC2.16, IC3.20, IC4.20, IC5.16, IC6.14, IC7.14, IC8.14, IC9.20, IC10.20, IC11.14, IC12.14, IC13.16, IC14.14, IC15.20, IN0.1, IO-ADDR-HL0.6, J2.38, J3.1, JP2.1, LO0.1, LO0.14, R2.2, R11.1, R12.1, R13.1, R14.1, R15.1, RN2.1, RN3.1, S0.1, S1.1, S2.1, S3.1, S4.1, S5.1, S6.1, S7.1, TM1.1, X1.A2, X1.A31, X1.B2, X1.B31, X1.C2, X1.C31, X2.2, X2.15, Y1.8
